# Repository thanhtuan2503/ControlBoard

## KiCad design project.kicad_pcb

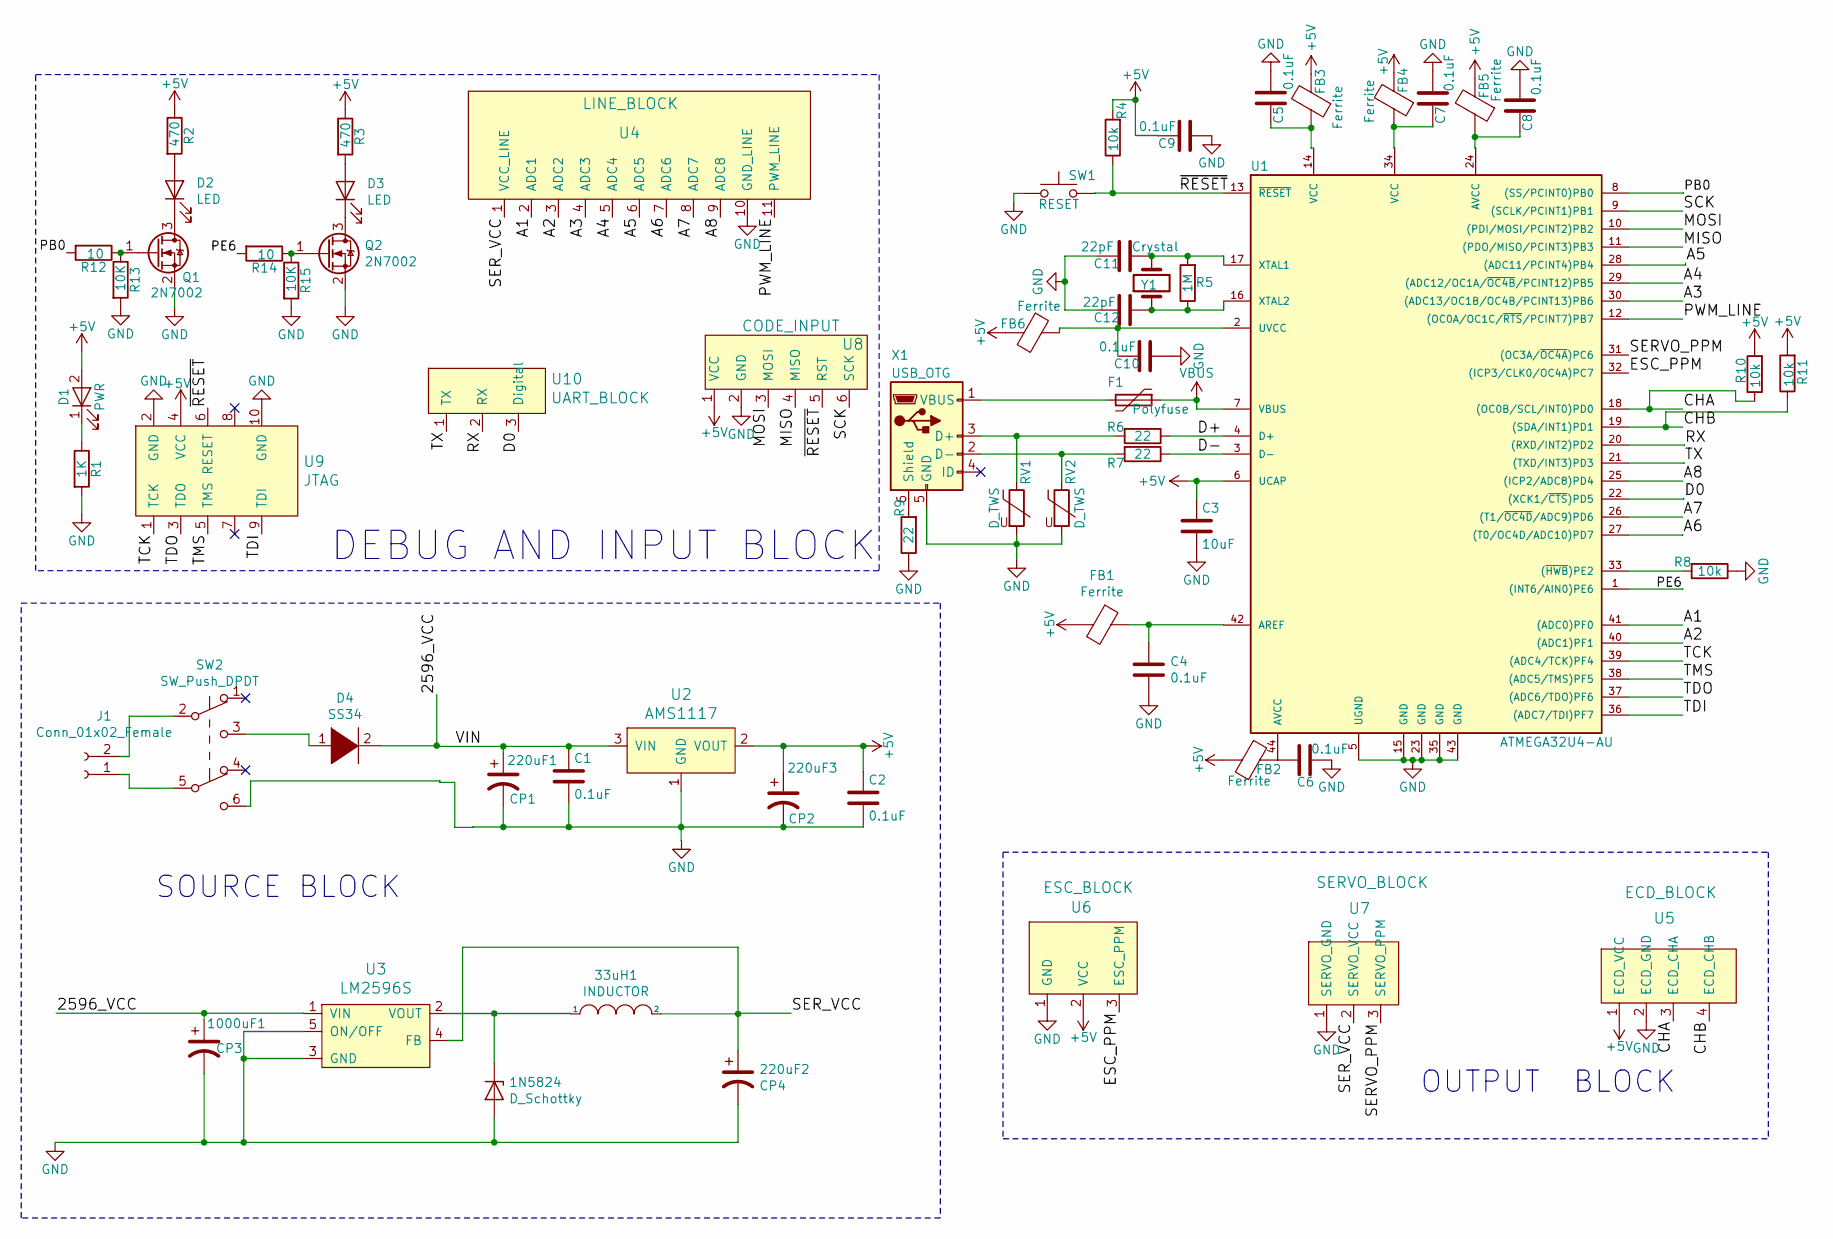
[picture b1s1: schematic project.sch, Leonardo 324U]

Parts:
1N5824: D_Schottky; SS34_SMC
33uH1: INDUCTOR; L_12x12mm_H8mm
220uF1: CP1; C_Elec_6.3x7.7
220uF2: CP4; C_Elec_6.3x7.7
220uF3: CP2; C_Elec_6.3x7.7
1000uF1: CP3; C_Elec_10x10.2
C1, C2, C4, C5, C6, C7, C8, C9, C10: 0.1uF; C_1206_3216Metric
C3: 10uF; C_1206_3216Metric
C11, C12: 22pF; C_1206_3216Metric
D1: PWR; LED_1206_3216Metric
D2, D3: LED; LED_1206_3216Metric
D4: SS34; SS34_SMC
F1: Polyfuse; R_1206_HandSoldering
FB1, FB2, FB3, FB4, FB5, FB6: Ferrite; FerriteBead
J1: Conn_01x02_Female; TerminalBlock_bornier-2_P5.08mm
Q1, Q2: 2N7002; SOT-23
R1: 1K; R_1206_3216Metric
R2, R3: 470; R_1206_3216Metric
R4, R8, R10, R11: 10k; R_1206_3216Metric
R5: 1M; R_1206_3216Metric
R6, R7, R9: 22; R_1206_3216Metric
R12, R14: 10; R_1206_3216Metric
R13, R15: 10K; R_1206_3216Metric
RV1, RV2: D_TWS; R_0805_HandSoldering
SW1: RESET; SW_SPST_PTS645
SW2: SW_Push_DPDT; Switch
U1: ATMEGA32U4-AU; TQFP-44_10x10mm_Pitch0.8mm
U2: AMS1117
U3: LM2596S; LM2596S-5V
U4: LINE_BLOCK; PinHeader_1x11_P2.54mm_Vertical_SMD_Pin1Right
U5: ECD_BLOCK; TerminalBlock_bornier-4_P5.08mm
U6: ESC_BLOCK; TerminalBlock_bornier-3_P5.08mm
U7: SERVO_BLOCK; TerminalBlock_bornier-3_P5.08mm
U8: CODE_INPUT; PinHeader_2x03_P2.54mm_Vertical_SMD
U9: JTAG; PinHeader_2x05_P2.54mm_Vertical_SMD
U10: UART_BLOCK
X1: USB_OTG; USB_Micro-B_Molex-105017-0001
Y1: Crystal

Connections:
+5V: 220uF3.1, C2.1, C3.1, C9.2, D1.2 (A), FB1.2, FB2.2, FB3.2, FB4.2, FB5.2, FB6.2, R2.1, R3.1, R4.2, R10.2, R11.2, U1.6 (UCAP), U2.2 (VOUT), U5.1 (ECD_VCC), U6.2 (VCC), U8.1 (VCC), U9.4 (VCC)
/2596_VCC: 220uF1.1, 1000uF1.1, C1.1, D4.2 (A), U2.3 (VIN), U3.1 (VIN)
/A1: U1.41 ((ADC0)PF0), U4.2 (ADC1)
/A2: U1.40 ((ADC1)PF1), U4.3 (ADC2)
/A3: U1.30 ((ADC13/OC1B/OC4B/PCINT13)PB6), U4.4 (ADC3)
/A4: U1.29 ((ADC12/OC1A/~OC4B~/PCINT12)PB5), U4.5 (ADC4)
/A5: U1.28 ((ADC11/PCINT4)PB4), U4.6 (ADC5)
/A6: U1.27 ((T0/OC4D/ADC10)PD7), U4.7 (ADC6)
/A7: U1.26 ((T1/~OC4D~/ADC9)PD6), U4.8 (ADC7)
/A8: U1.25 ((ICP2/ADC8)PD4), U4.9 (ADC8)
/CHA: R10.1, U1.18 ((OC0B/SCL/INT0)PD0), U5.3 (ECD_CHA)
/CHB: R11.1, U1.19 ((SDA/INT1)PD1), U5.4 (ECD_CHB)
/D+: R6.1, U1.4 (D+)
/D-: R7.1, U1.3 (D-)
/ESC_PPM: U1.32 ((ICP3/CLK0/OC4A)PC7), U6.3 (ESC_PPM)
/MISO: U1.11 ((PDO/MISO/PCINT3)PB3), U8.4 (MISO)
/MOSI: U1.10 ((PDI/MOSI/PCINT2)PB2), U8.3 (MOSI)
/PB0: R12.2, U1.8 ((SS/PCINT0)PB0)
/PE6: R14.2, U1.1 ((INT6/AIN0)PE6)
/PWM_LINE: U1.12 ((OC0A/OC1C/~RTS~/PCINT7)PB7), U4.11 (PWM_LINE)
/SCK: U1.9 ((SCLK/PCINT1)PB1), U8.6 (SCK)
/SERVO_PPM: U1.31 ((OC3A/~OC4A~)PC6), U7.3 (SERVO_PPM)
/SER_VCC: 33uH1.2, 220uF2.1, U3.4 (FB), U4.1 (VCC_LINE), U7.2 (SERVO_VCC)
/TCK: U1.39 ((ADC4/TCK)PF4), U9.1 (TCK)
/TDI: U1.36 ((ADC7/TDI)PF7), U9.9 (TDI)
/TDO: U1.37 ((ADC6/TDO)PF6), U9.3 (TDO)
/TMS: U1.38 ((ADC5/TMS)PF5), U9.5 (TMS)
/~RESET: R4.1, SW1.2, U1.13 (~RESET~), U8.5 (RST), U9.6 (RESET)
GND: 1N5824.2 (A), 220uF1.2, 220uF2.2, 220uF3.2, 1000uF1.2, C1.2, C2.2, C3.2, C4.2, C5.1, C6.1, C7.1, C8.1, C9.1, C10.1, C11.2, C12.2, Q1.2 (S), Q2.2 (S), R1.2, R8.1, R9.1, R13.2, R15.2, RV1.2, RV2.2, SW1.1, SW2.6 (C), U1.5 (UGND), U1.15 (GND), U1.23 (GND), U1.35 (GND), U1.43 (GND), U2.1 (GND), U3.3 (GND), U3.5 (ON/OFF), U4.10 (GND_LINE), U5.2 (ECD_GND), U6.1 (GND), U7.1 (SERVO_GND), U8.2 (GND), U9.2 (GND), U9.10 (GND), X1.5 (GND); also elsewhere on the board
unnamed: 1N5824.1 (K), 33uH1.1, U3.2 (VOUT)
unnamed: C4.1, FB1.1, U1.42 (AREF)
unnamed: C5.2, FB3.1, U1.14 (VCC)
unnamed: C6.2, FB2.1, U1.44 (AVCC)
unnamed: C7.2, FB4.1, U1.34 (VCC)
unnamed: C8.2, FB5.1, U1.24 (AVCC)
unnamed: C10.2, FB6.1, U1.2 (UVCC)
unnamed: D1.1 (K), R1.1
unnamed: D2.1 (K), Q1.3 (D)
unnamed: D2.2 (A), R2.2
unnamed: D3.1 (K), Q2.3 (D)
unnamed: D3.2 (A), R3.2
unnamed: D4.1 (K), SW2.3 (C)
unnamed: F1.2, X1.1 (VBUS)
unnamed: J1.1, SW2.5 (B)
unnamed: J1.2, SW2.2 (B)
unnamed: Q1.1 (G), R12.1, R13.1
unnamed: Q2.1 (G), R14.1, R15.1
unnamed 47: C12.1, R5.1, U1.16 (XTAL2), Y1.1; also elsewhere on the board
unnamed 48: C11.1, R5.2, U1.17 (XTAL1), Y1.2; also elsewhere on the board
unnamed: R6.2, RV1.1, X1.3 (D+)
unnamed: R7.2, RV2.1, X1.2 (D-)
unnamed: R8.2, U1.33 ((~HWB~)PE2)
unnamed: R9.2, X1.6 (Shield)
unnamed: U1.20 ((RXD/INT2)PD2), U10.2 (RX)
unnamed: U1.21 ((TXD/INT3)PD3), U10.1 (TX)
unnamed: U1.22 ((XCK1/~CTS~)PD5), U10.3 (Digital)
VBUS: F1.1, U1.7 (VBUS)

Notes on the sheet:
SOURCE BLOCK
OUTPUT BLOCK
DEBUG AND INPUT BLOCK

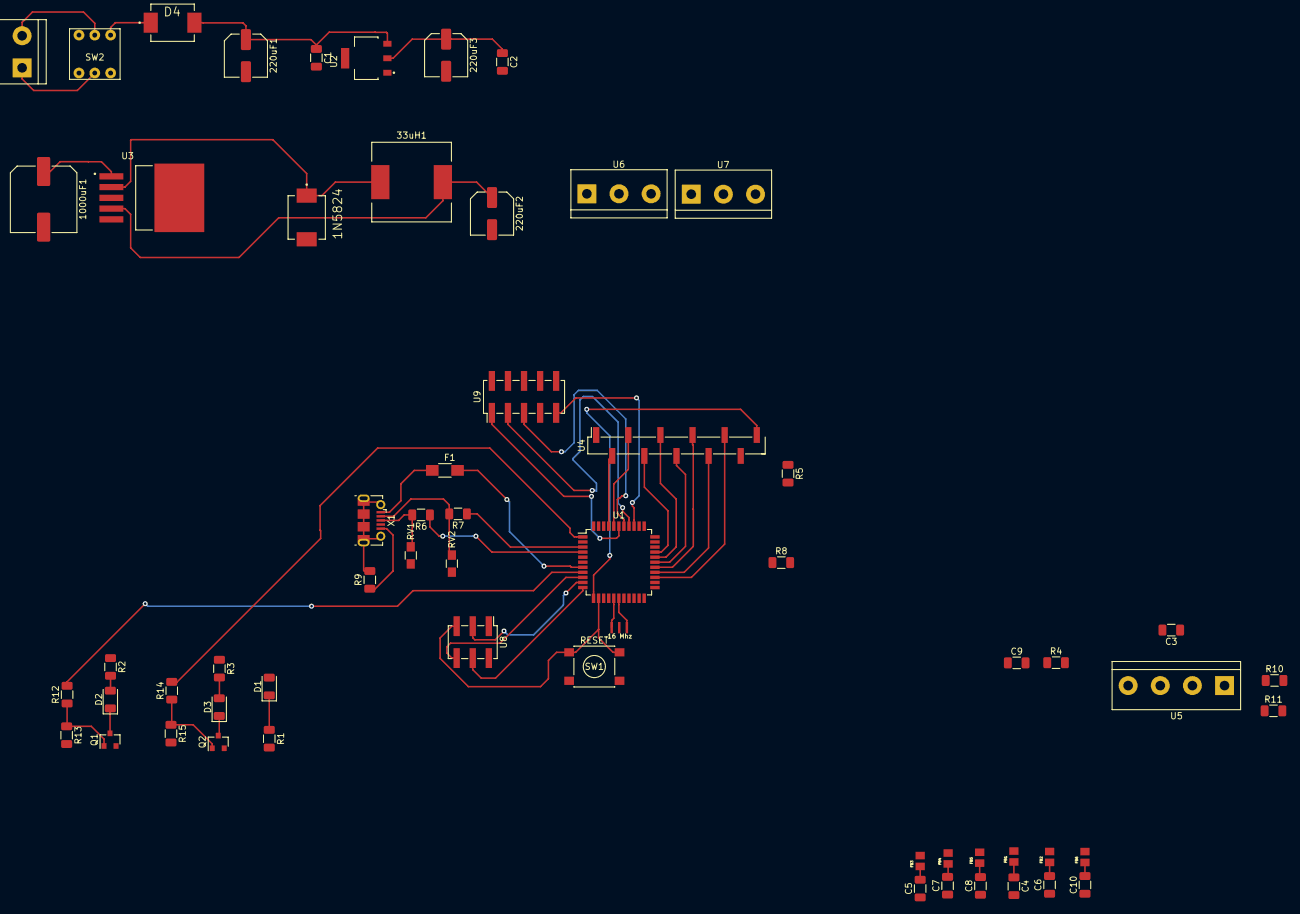
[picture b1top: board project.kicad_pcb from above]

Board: 2 copper layers, 60 parts (0 on the bottom side), 54 nets.

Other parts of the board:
Y1_5535: 16 Mhz; Resonator_SMD_CTSC_1.3mmx3.2mm

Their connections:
GND: Y1_5535.2; also elsewhere on the board
unnamed 47: Y1_5535.3; also elsewhere on the board
unnamed 48: Y1_5535.1; also elsewhere on the board

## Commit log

2020-09-08 Layout1
2022-01-22 Add new txt file for test!
